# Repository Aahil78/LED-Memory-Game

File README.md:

# LED Memory Game
This is a simple LED Memory Game PCB that sits on top of an Arduino UNO, it has 4 LEDs (Red, Green, Blue, Yellow), 4 Buttons, a vibration motor, dc barel jack, 4 resistors, and that's it!
# Slack Username
- @Aahil
- Slack ID: U08GLNF2JMU
# Pictures

# Schematic

# PCB

# Features
- Easy to assemble
- Fun to play
- Randomized sequence each time
- Has a time limit to enter sequence fr better gameplay
- Cool!

# BOM
- 4 LEDs (Red, Green, Blue, Yellow)
- 4 Resistors (220ohm)
- 4 Pushbuttons
- 1 Vibration Motor
- 1 DC Barrel Jack
- 1 Arduino UNO
- Thats it! (except for a PCB ofc)

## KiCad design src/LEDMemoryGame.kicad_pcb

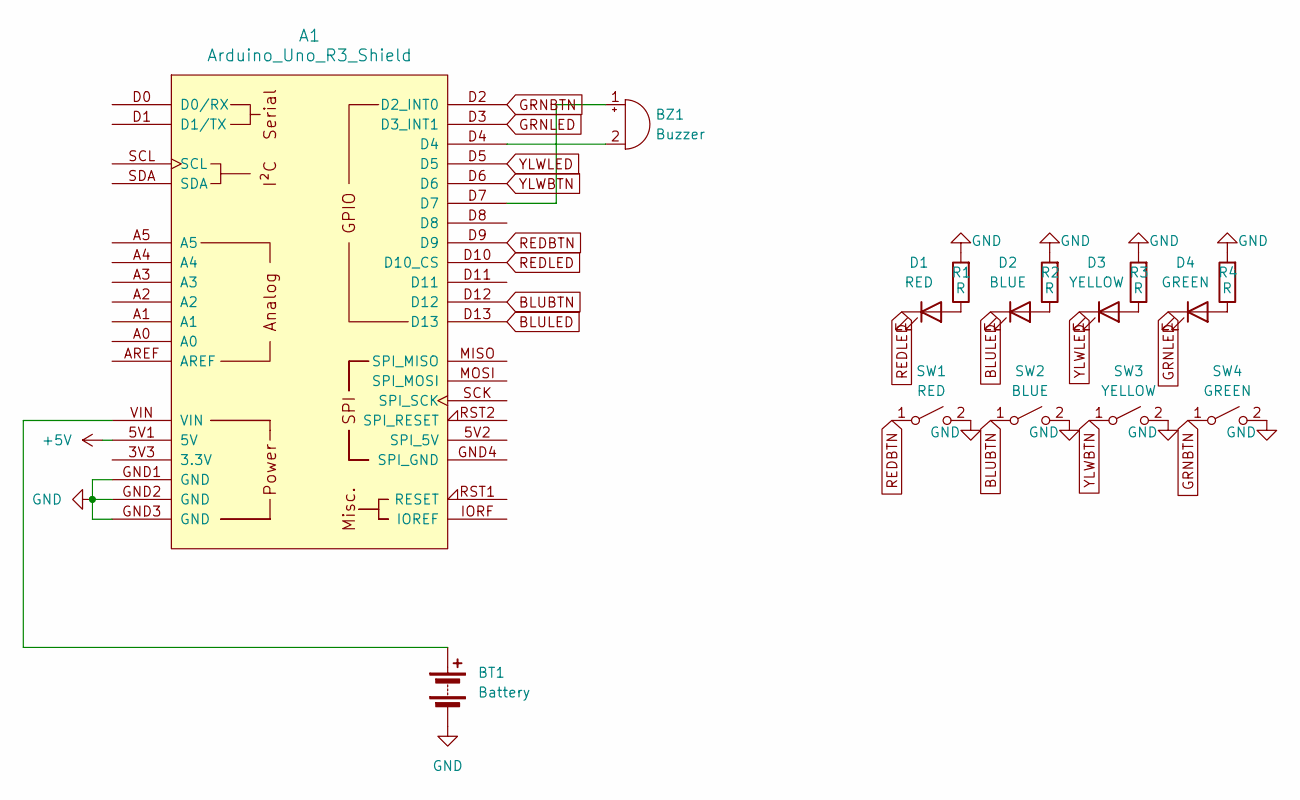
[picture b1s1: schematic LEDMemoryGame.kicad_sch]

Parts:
A1: Arduino_Uno_R3_Shield
BT1: Battery; BarrelJack_CUI_PJ-063AH_Horizontal_CircularHoles
BZ1: Buzzer; Buzzer_TDK_PS1240P02BT_D12.2mm_H6.5mm
D1: RED; LED_D5.0mm
D2: BLUE; LED_D5.0mm
D3: YELLOW; LED_D5.0mm
D4: GREEN; LED_D5.0mm
R1, R2, R3, R4: R; R_Axial_DIN0204_L3.6mm_D1.6mm_P7.62mm_Horizontal
SW1: RED; SW_Tactile_Straight_KSL0Axx1LFTR
SW2: BLUE; SW_Tactile_Straight_KSL0Axx1LFTR
SW3: YELLOW; SW_Tactile_Straight_KSL0Axx1LFTR
SW4: GREEN; SW_Tactile_Straight_KSL0Axx1LFTR

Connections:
+5V: A1.5V1 (5V)
BLUBTN: A1.D12, SW2.1 (A)
BLULED: A1.D13, D2.1 (K)
GND: A1.GND1 (GND), A1.GND2 (GND), A1.GND3 (GND), BT1.2 (-), R1.2, R2.2, R3.2, R4.2, SW1.2 (B), SW2.2 (B), SW3.2 (B), SW4.2 (B)
GRNBTN: A1.D2 (D2_INT0), SW4.1 (A)
GRNLED: A1.D3 (D3_INT1), D4.1 (K)
unnamed: A1.VIN, BT1.1 (+)
unnamed: A1.D7, BZ1.1 (+)
unnamed: A1.D4, BZ1.2 (-)
unnamed: D1.2 (A), R1.1
unnamed: D2.2 (A), R2.1
unnamed: D3.2 (A), R3.1
unnamed: D4.2 (A), R4.1
REDBTN: A1.D9, SW1.1 (A)
REDLED: A1.D10 (D10_CS), D1.1 (K)
YLWBTN: A1.D6, SW3.1 (A)
YLWLED: A1.D5, D3.1 (K)

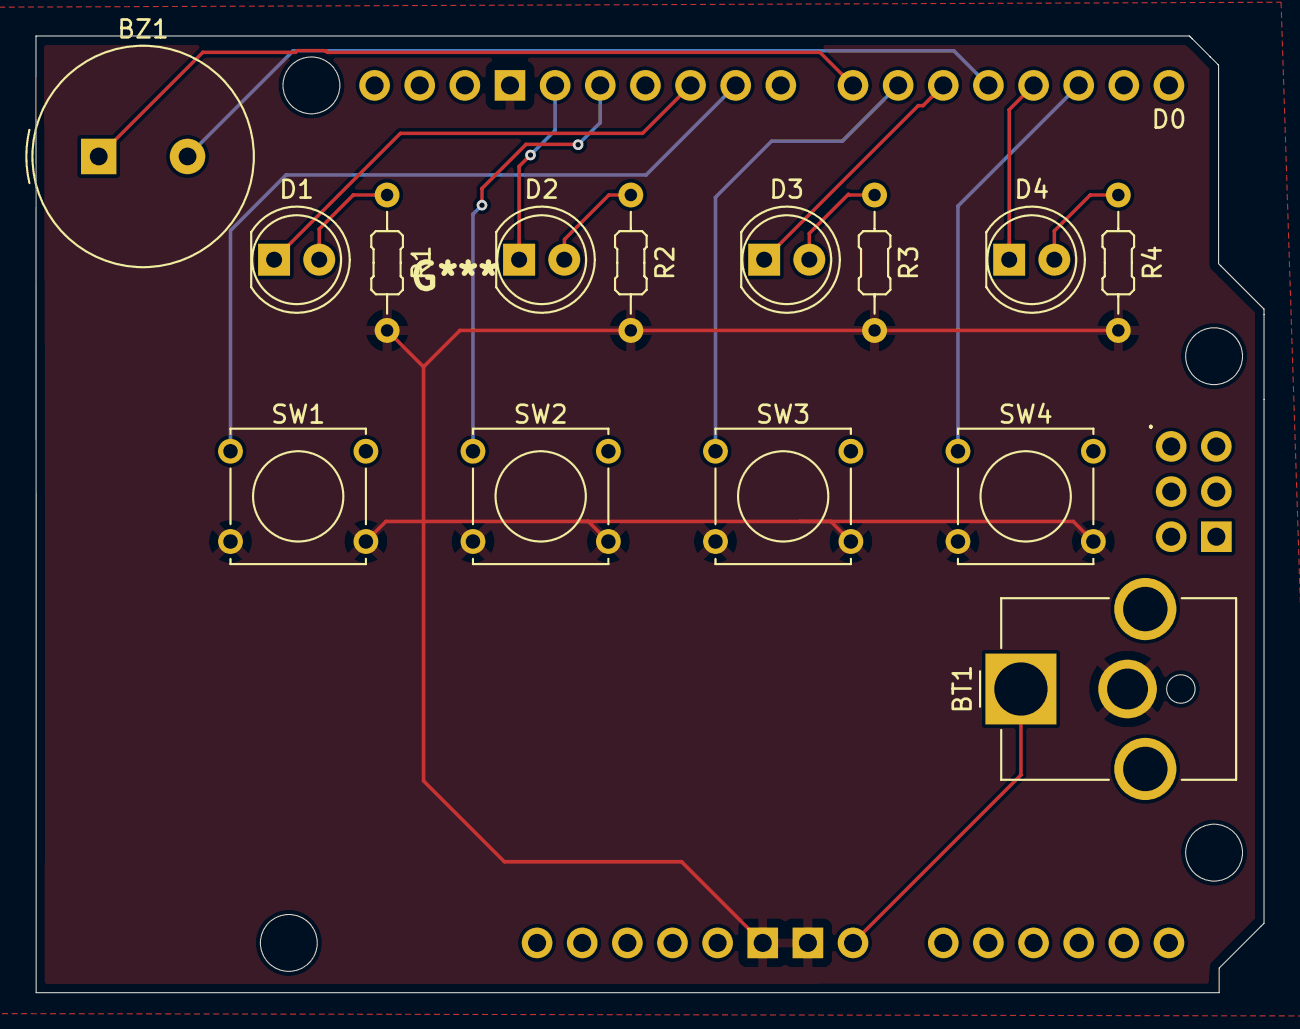
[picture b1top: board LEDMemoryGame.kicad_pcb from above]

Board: 2 copper layers, 69.1 x 53.8 mm, 15 parts (0 on the bottom side), 16 nets.

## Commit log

2025-04-22 Add all files
2025-04-22 Rename LEDMemoryGame.kicad_prl to src/LEDMemoryGame.kicad_prl
2025-04-22 Rename LEDMemoryGame.kicad_pro to src/LEDMemoryGame.kicad_pro
2025-04-22 Rename gerber.zip to production/gerber.zip
2025-04-22 Rename LEDMemoryGame__Assembly.pdf to plots/LEDMemoryGame__Assembly.pdf
2025-04-30 Update repo
    Updated all the files to make the PCB Better
